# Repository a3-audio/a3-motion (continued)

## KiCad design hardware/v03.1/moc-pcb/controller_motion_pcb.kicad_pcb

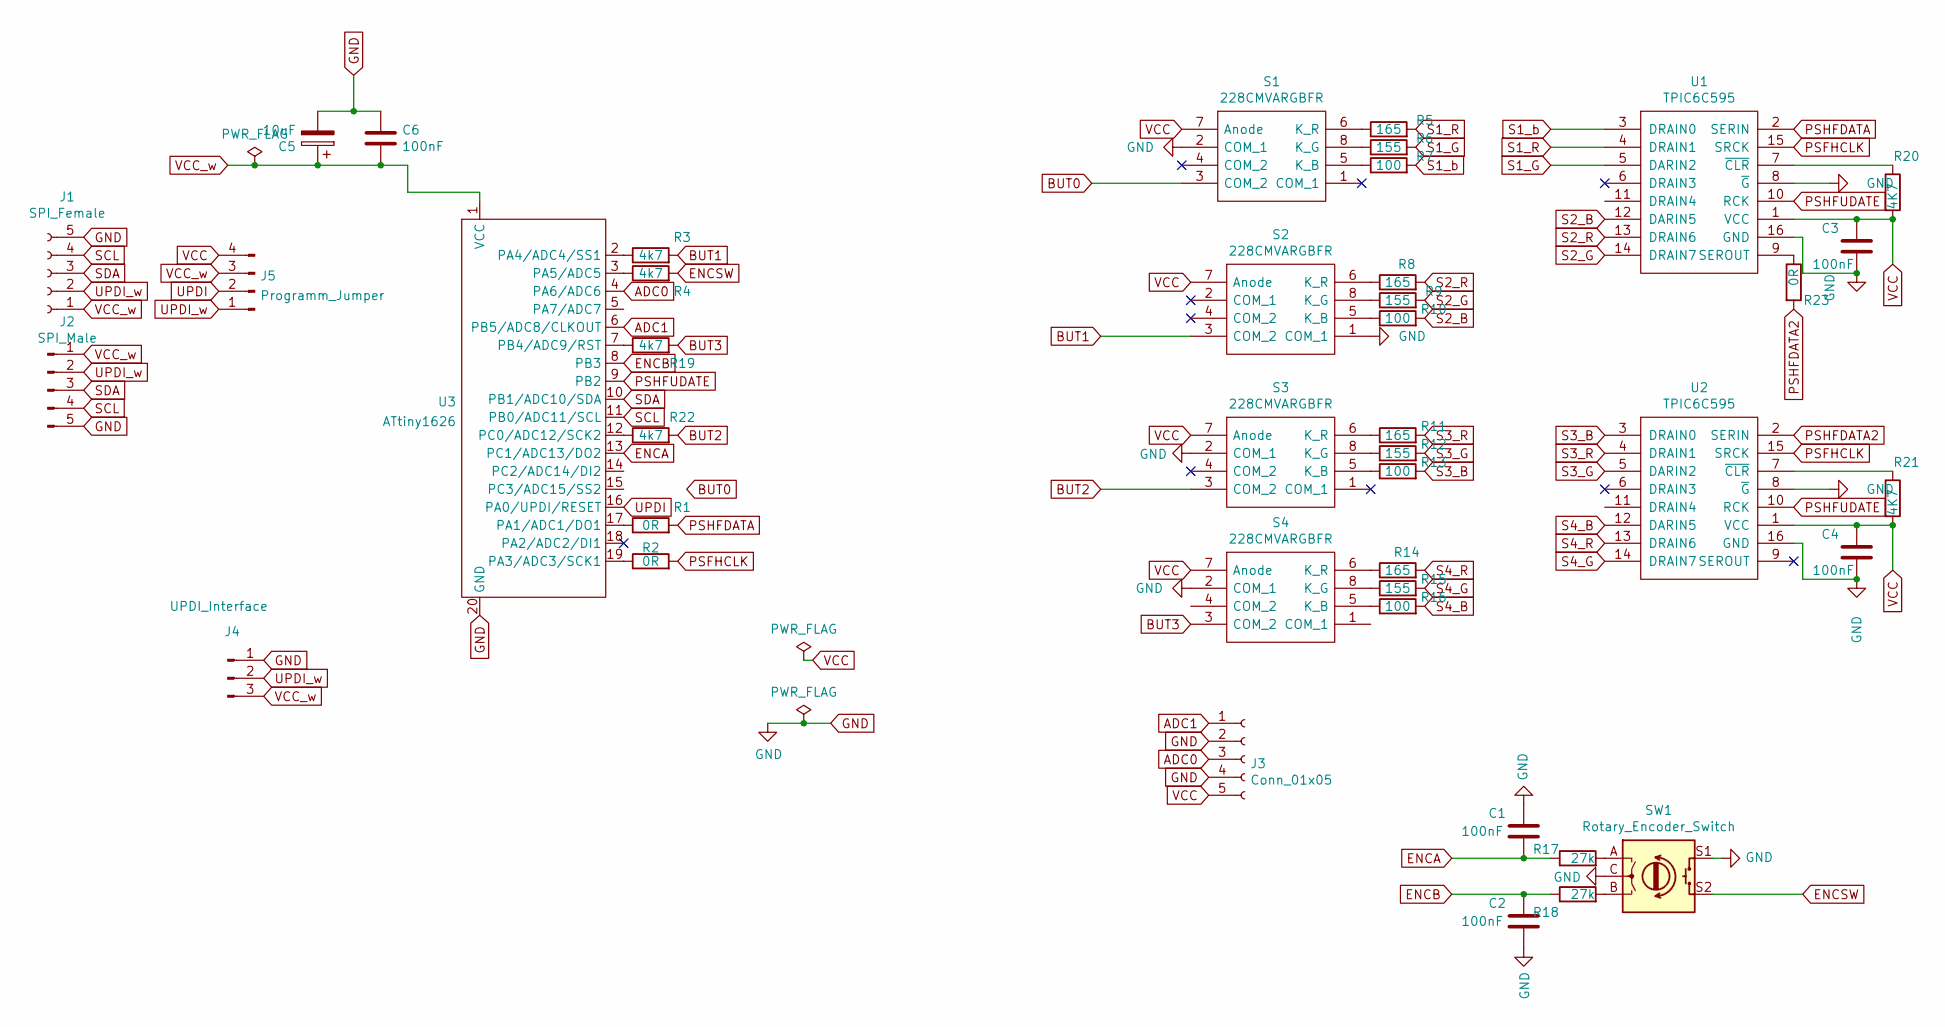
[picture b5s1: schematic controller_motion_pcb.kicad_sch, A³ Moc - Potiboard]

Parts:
C1, C2, C3, C4, C6: 100nF; C_1206_3216Metric_Pad1.33x1.80mm_HandSolder
C5: 10uF; CP_Radial_D4.0mm_P1.50mm
J1: SPI_Female; PinSocket_1x05_P2.54mm_Horizontal
J2: SPI_Male; PinHeader_1x05_P2.54mm_Horizontal
J3: Conn_01x05; JST_XH_B5B-XH-A_1x05_P2.50mm_Vertical
J4: UPDI_Interface; PinHeader_1x03_P2.54mm_Vertical
J5: Programm_Jumper; PinHeader_2x02_P2.54mm_Vertical
R1, R2, R23: 0R; R_1206_3216Metric_Pad1.30x1.75mm_HandSolder
R3, R4, R19, R22: 4k7; R_1206_3216Metric_Pad1.30x1.75mm_HandSolder
R5, R8, R11, R14: 165; R_1206_3216Metric_Pad1.30x1.75mm_HandSolder
R6, R9, R12, R15: 155; R_1206_3216Metric_Pad1.30x1.75mm_HandSolder
R7, R10, R13, R16: 100; R_1206_3216Metric_Pad1.30x1.75mm_HandSolder
R17, R18: 27k; R_1206_3216Metric_Pad1.30x1.75mm_HandSolder
R20, R21: 4K7; R_1206_3216Metric_Pad1.30x1.75mm_HandSolder
S1, S2, S3, S4: 228CMVARGBFR; 228CMVARGBFR_SMD; Mouser Part Number 774-228CMVARGBFR
SW1: Rotary_Encoder_Switch; PEC11R4230KS0024
U1, U2: TPIC6C595; SOIC-16_3.9x9.9mm_P1.27mm
U3: ATtiny1626; attiny1626

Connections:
ADC0: J3.3, U3.4 (PA6/ADC6)
BUT0: S1.3 (COM_2)
BUT1: R3.2, S2.3 (COM_2)
BUT2: R22.2, S3.3 (COM_2)
BUT3: R19.2, S4.3 (COM_2)
ENCA: C1.2, R17.1, U3.13 (PC1/ADC13/DO2)
ENCB: C2.1, R18.1, U3.8 (PB3)
ENCSW: R4.2, SW1.S2
GND: C1.1, C2.2, C3.2, C4.2, C5.2, C6.1, J1.5, J2.5, J3.2, J3.4, J4.1, S1.2 (COM_1), S2.1 (COM_1), S3.2 (COM_1), S4.2 (COM_1), SW1.C, SW1.S1, U1.8 (~G), U1.16 (GND), U2.8 (~G), U2.16 (GND), U3.20 (GND)
unnamed: R1.1, U3.17 (PA1/ADC1/DO1)
unnamed: R2.1, U3.19 (PA3/ADC3/SCK1)
unnamed: R3.1, U3.2 (PA4/ADC4/SS1)
unnamed: R4.1, U3.3 (PA5/ADC5)
unnamed: R5.1, S1.6 (K_R)
unnamed: R6.1, S1.8 (K_G)
unnamed: R7.1, S1.5 (K_B)
unnamed: R8.1, S2.6 (K_R)
unnamed: R9.1, S2.8 (K_G)
unnamed: R10.1, S2.5 (K_B)
unnamed: R11.1, S3.6 (K_R)
unnamed: R12.1, S3.8 (K_G)
unnamed: R13.1, S3.5 (K_B)
unnamed: R14.1, S4.6 (K_R)
unnamed: R15.1, S4.8 (K_G)
unnamed: R16.1, S4.5 (K_B)
unnamed: R17.2, SW1.A
unnamed: R18.2, SW1.B
unnamed: R19.1, U3.7 (PB4/ADC9/RST)
unnamed: R20.1, U1.7 (~CLR)
unnamed: R21.1, U2.7 (~CLR)
unnamed: R22.1, U3.12 (PC0/ADC12/SCK2)
unnamed: R23.1, U1.9 (SEROUT)
PSFHCLK: R2.2, U1.15 (SRCK), U2.15 (SRCK)
PSHFDATA: R1.2, U1.2 (SERIN)
PSHFDATA2: R23.2, U2.2 (SERIN)
PSHFUDATE: U1.10 (RCK), U2.10 (RCK), U3.9 (PB2)
S1_G: R6.2, U1.5 (DARIN2)
S1_R: R5.2, U1.4 (DRAIN1)
S1_b: R7.2, U1.3 (DRAIN0)
S2_B: R10.2, U1.12 (DARIN5)
S2_G: R9.2, U1.14 (DRAIN7)
S2_R: R8.2, U1.13 (DRAIN6)
S3_B: R13.2, U2.3 (DRAIN0)
S3_G: R12.2, U2.5 (DARIN2)
S3_R: R11.2, U2.4 (DRAIN1)
S4_B: R16.2, U2.12 (DARIN5)
S4_G: R15.2, U2.14 (DRAIN7)
S4_R: R14.2, U2.13 (DRAIN6)
SCL: J1.4, J2.4, U3.11 (PB0/ADC11/SCL)
SDA: J1.3, J2.3, U3.10 (PB1/ADC10/SDA)
UPDI: J5.2, U3.16 (PA0/UPDI/RESET)
UPDI_w: J1.2, J2.2, J4.2, J5.1
VCC_w: C5.1, C6.2, J1.1, J2.1, J4.3, J5.3, U3.1 (VCC)

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
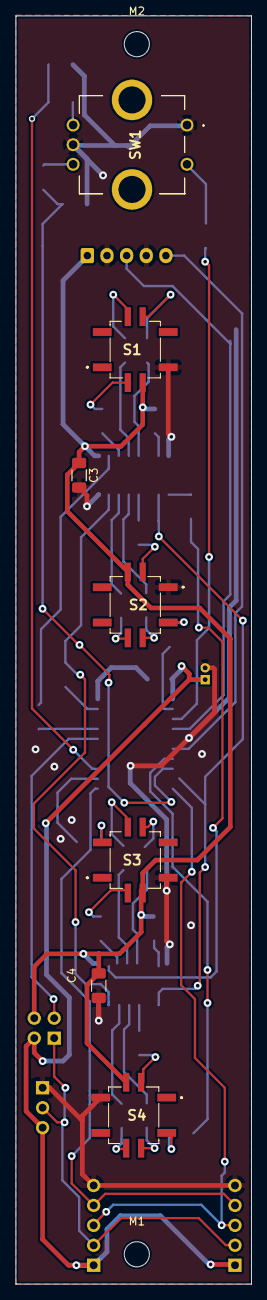
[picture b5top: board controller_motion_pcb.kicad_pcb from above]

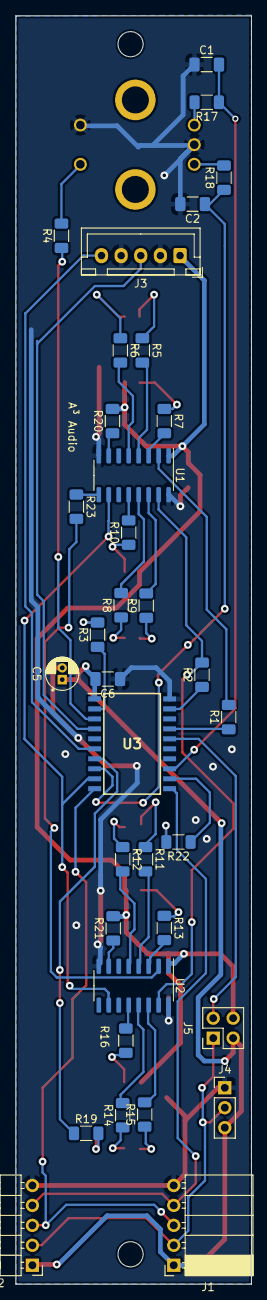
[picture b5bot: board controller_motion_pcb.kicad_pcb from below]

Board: 2 copper layers, 30.0 x 161.5 mm, 44 parts (35 on the bottom side), 54 nets.

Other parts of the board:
M1, M2: MountingHole_3.2mm_M3
